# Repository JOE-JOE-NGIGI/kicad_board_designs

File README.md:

# kicad_board_designs
A repository of hardware design projects I have worked on.
Printed Circuit Boards(PCBs) have been designed using KiCad Version 5.1.12.

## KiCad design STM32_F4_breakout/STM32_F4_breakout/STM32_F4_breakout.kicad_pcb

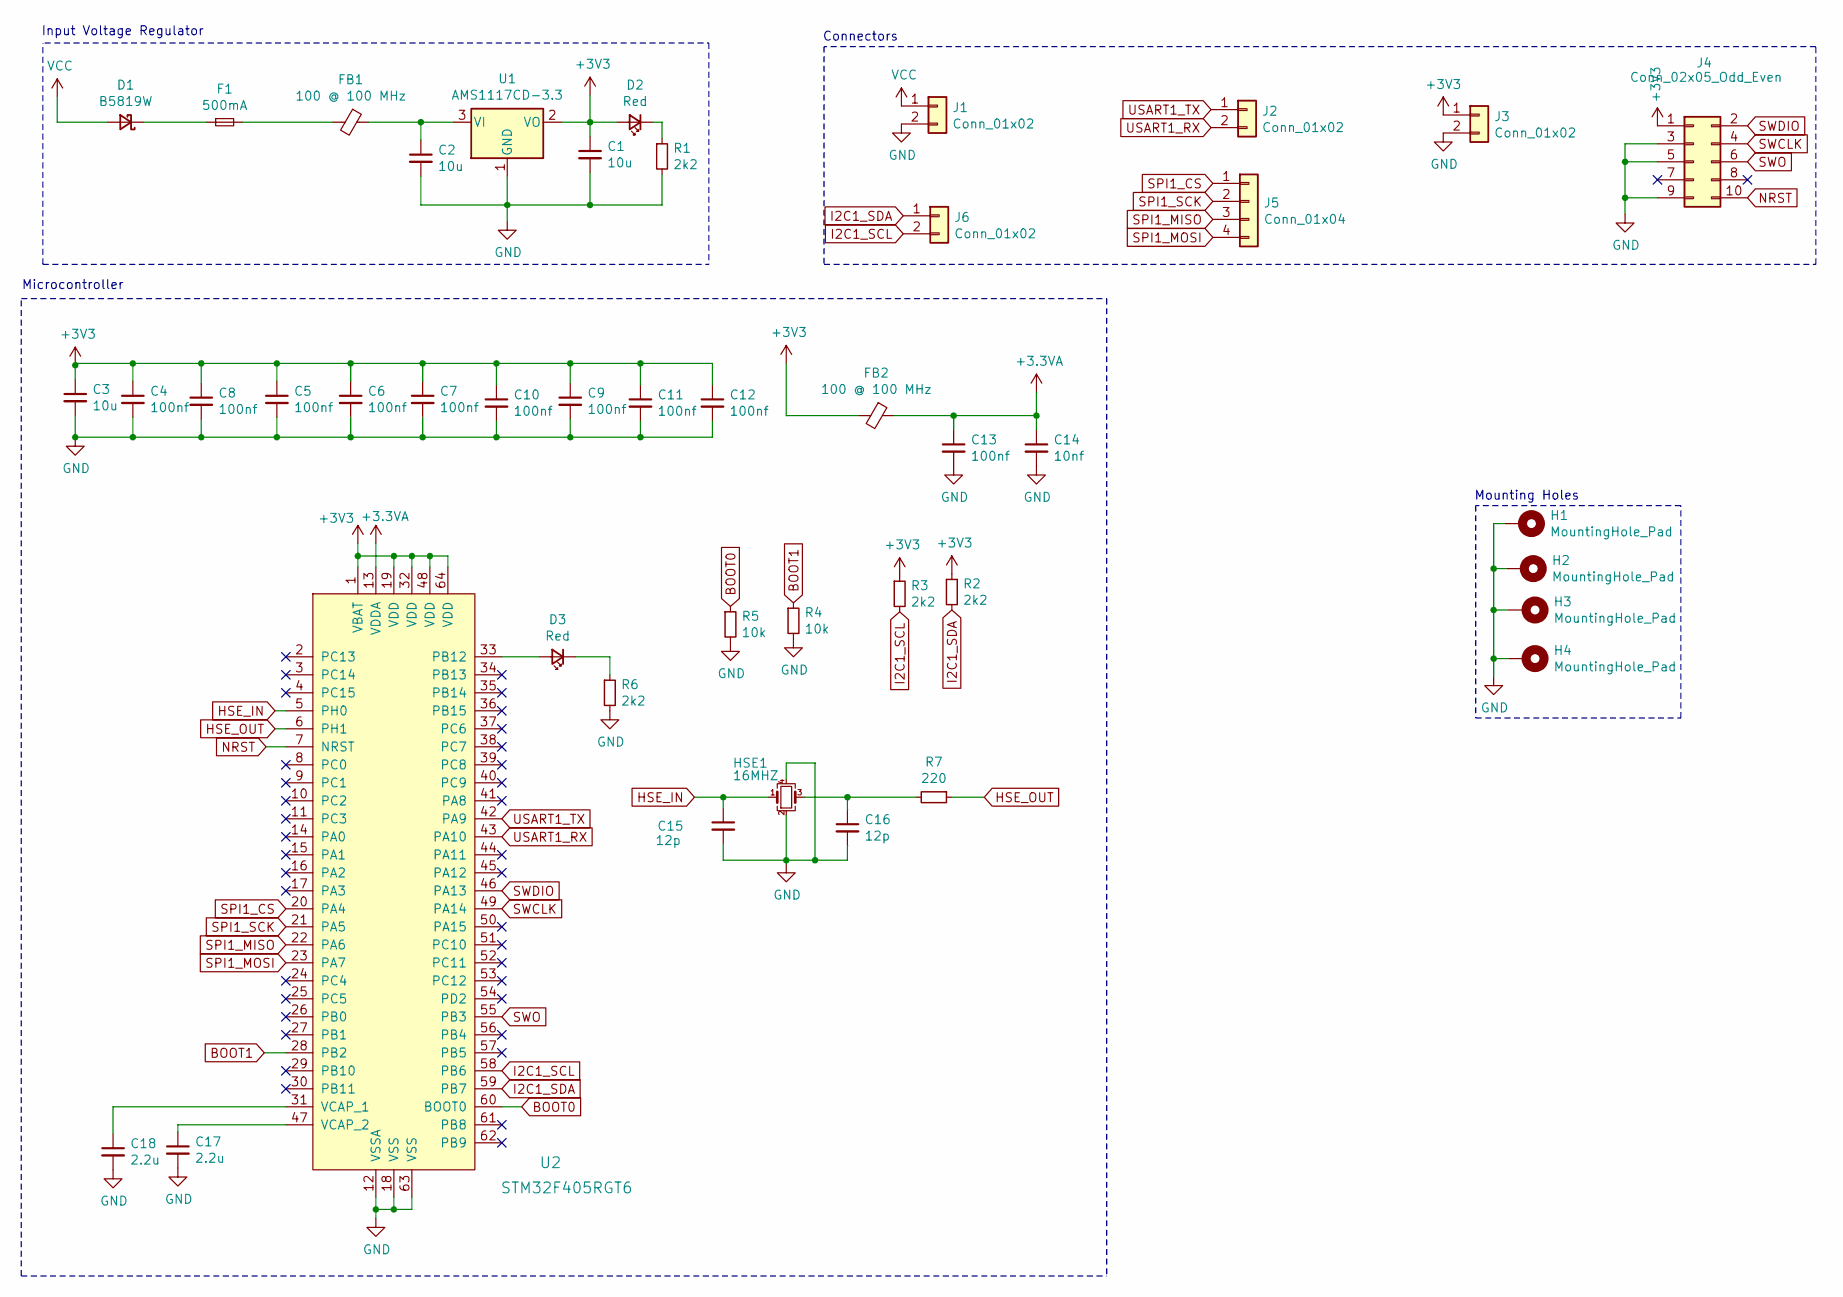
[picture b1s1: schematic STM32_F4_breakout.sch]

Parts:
C1, C2: 10u; C_0805_2012Metric
C3: 10u; C_0603_1608Metric
C4, C5, C6, C7, C8, C9, C10, C11, C12, C13: 100nf; C_0402_1005Metric
C14: 10nf; C_0402_1005Metric
C15, C16: 12p; C_0402_1005Metric
C17, C18: 2.2u; C_0603_1608Metric
D1: B5819W; D_SOD-123
D2, D3: Red; LED_0603_1608Metric
F1: 500mA; Fuse_0603_1608Metric
FB1, FB2: 100 @ 100 MHz; Fuse_0805_2012Metric
H1, H2, H3, H4: MountingHole_Pad; MountingHole_4.3mm_M4_Pad_Via
HSE1: 16MHZ; Crystal_SMD_3225-4Pin_3.2x2.5mm
J1, J2, J3, J6: Conn_01x02; PinHeader_1x02_P2.54mm_Vertical
J4: Conn_02x05_Odd_Even; PinHeader_2x05_P1.27mm_Vertical_SMD
J5: Conn_01x04; PinHeader_1x04_P2.54mm_Vertical
R1, R6: 2k2; R_0603_1608Metric
R2, R3: 2k2; R_0402_1005Metric
R4, R5: 10k; R_0402_1005Metric
R7: 220; R_0402_1005Metric
U1: AMS1117CD-3.3; TO-252-3_TabPin2
U2: STM32F405RGT6; LQFP-64_10x10mm; MPN STM32F405RGT6; Digi-Key_PN 497-11767-ND

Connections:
+3.3VA: C13.1, C14.1, FB2.1, U2.13 (VDDA)
+3V3: C1.1, C3.1, C4.1, C5.1, C6.1, C7.1, C8.1, C9.1, C10.1, C11.1, C12.1, D2.2 (A), FB2.2, J3.1, J4.1, R2.1, R3.1, U1.2 (VO), U2.1 (VBAT), U2.19 (VDD), U2.32 (VDD), U2.48 (VDD), U2.64 (VDD)
BOOT0: R5.1, U2.60 (BOOT0)
BOOT1: R4.1, U2.28 (PB2)
GND: C1.2, C2.2, C3.2, C4.2, C5.2, C6.2, C7.2, C8.2, C9.2, C10.2, C11.2, C12.2, C13.2, C14.2, C15.2, C16.2, C17.2, C18.2, H1.1, H2.1, H3.1, H4.1, HSE1.2, HSE1.4, J1.2, J3.2, J4.3, J4.5, J4.9, R1.2, R4.2, R5.2, R6.2, U1.1 (GND), U2.12 (VSSA), U2.18 (VSS), U2.63 (VSS)
HSE_IN: C15.1, HSE1.1, U2.5 (PH0)
HSE_OUT: R7.1, U2.6 (PH1)
I2C1_SCL: J6.2, R3.2, U2.58 (PB6)
I2C1_SDA: J6.1, R2.2, U2.59 (PB7)
NRST: J4.10, U2.7 (NRST)
unnamed: C2.1, FB1.1, U1.3 (VI)
unnamed: C16.1, HSE1.3, R7.2
unnamed: C17.1, U2.47 (VCAP_2)
unnamed: C18.1, U2.31 (VCAP_1)
unnamed: D1.1 (K), F1.1
unnamed: D2.1 (K), R1.1
unnamed: D3.1 (K), R6.1
unnamed: D3.2 (A), U2.33 (PB12)
unnamed: F1.2, FB1.2
SPI1_CS: J5.1, U2.20 (PA4)
SPI1_MISO: J5.3, U2.22 (PA6)
SPI1_MOSI: J5.4, U2.23 (PA7)
SPI1_SCK: J5.2, U2.21 (PA5)
SWCLK: J4.4, U2.49 (PA14)
SWDIO: J4.2, U2.46 (PA13)
SWO: J4.6, U2.55 (PB3)
USART1_RX: J2.2, U2.43 (PA10)
USART1_TX: J2.1, U2.42 (PA9)
VCC: D1.2 (A), J1.1

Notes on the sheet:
Input Voltage Regulator
Microcontroller
Connectors
Mounting Holes

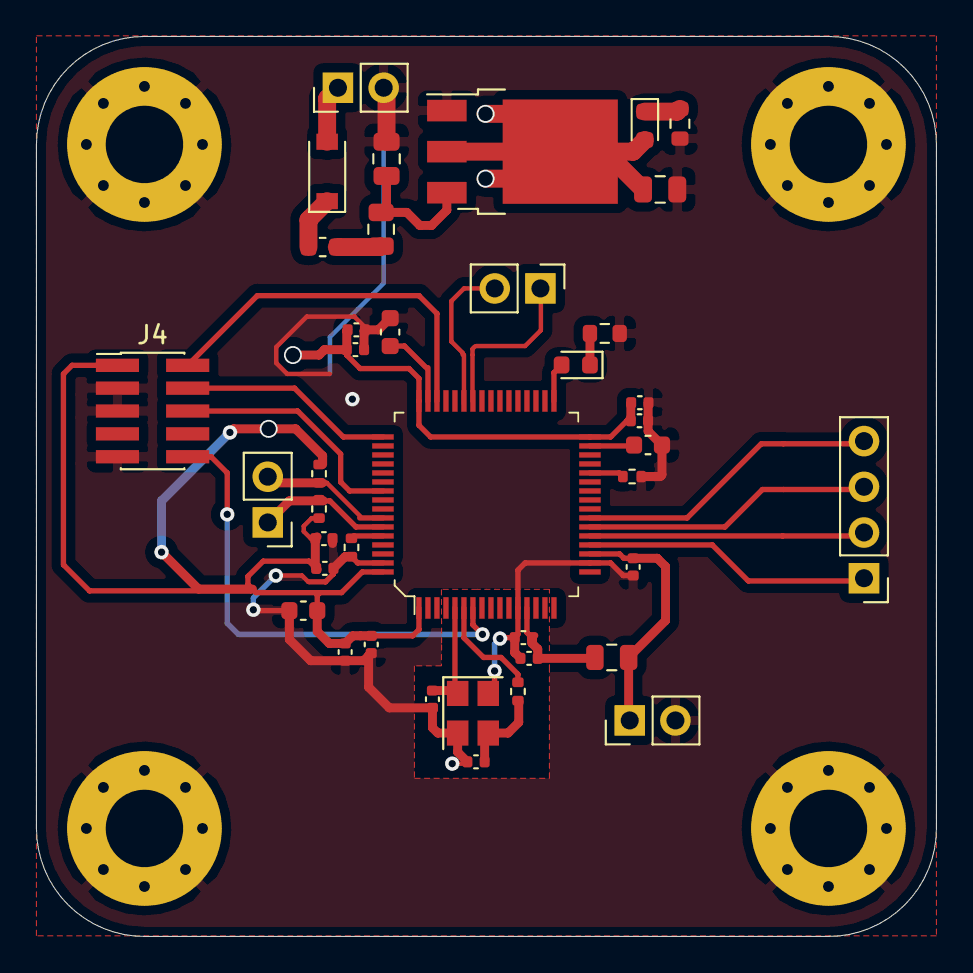
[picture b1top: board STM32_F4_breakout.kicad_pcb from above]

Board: 4 copper layers, 50.0 x 50.0 mm, 44 parts (0 on the bottom side), 29 nets.

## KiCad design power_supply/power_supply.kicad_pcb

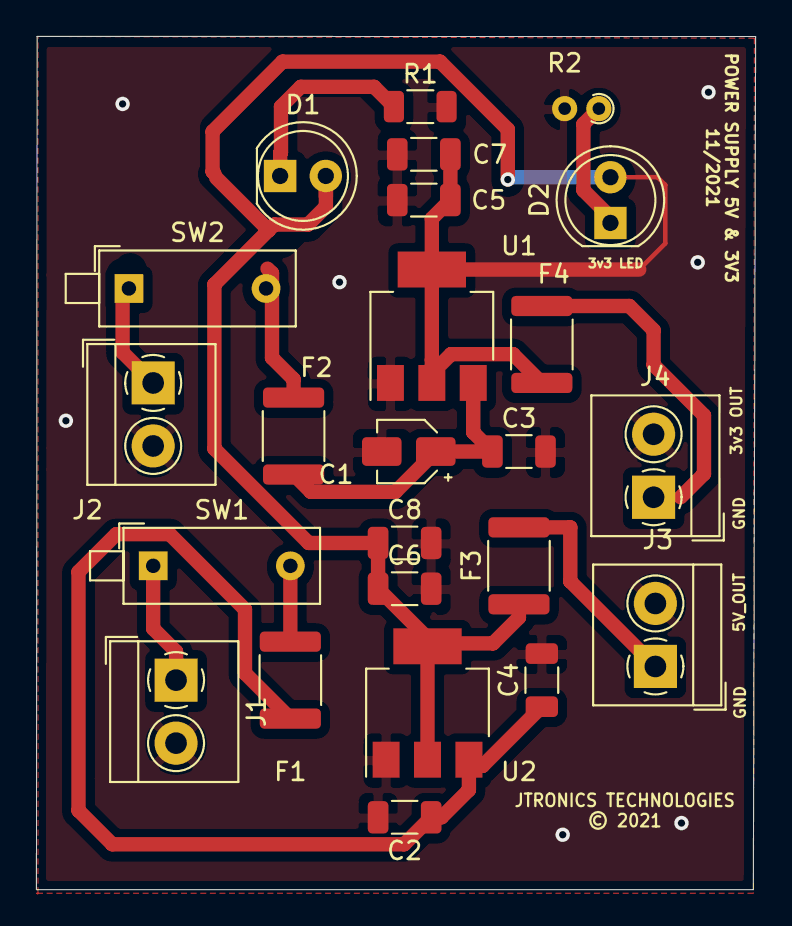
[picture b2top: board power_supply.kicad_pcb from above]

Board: 2 copper layers, 40.0 x 47.4 mm, 24 parts (0 on the bottom side), 12 nets.

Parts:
C1: 10u; CP_Elec_3x5.4
C2, C5, C6: 10u; C_1206_3216Metric
C3, C4: 100n; C_1206_3216Metric
C7, C8: 0.1u; C_1206_3216Metric
D1, D2: LED_Small; LED_D5.0mm
F1, F2, F3, F4: Fuse_Small; Fuse_1812_4532Metric
J1, J2, J3, J4: Conn_01x02; TerminalBlock_4Ucon_1x02_P3.50mm_Horizontal
R1: 1k; R_1206_3216Metric
R2: 1k; R_Axial_DIN0204_L3.6mm_D1.6mm_P1.90mm_Vertical
SW1, SW2: SW_DIP_x01; SW_DIP_SPSTx01_Piano_10.8x4.1mm_W7.62mm_P2.54mm
U1: LD1117S33TR_SOT223; SOT-223-3_TabPin2
U2: LD1117S50TR_SOT223; SOT-223-3_TabPin2

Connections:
+3V3: C5.1, C6.1, C7.1, C8.1, D1.2, D2.2, F3.1, F4.1, U1.2, U2.2
/3v3_out: F4.2, J4.1
/5V_out: F3.2, J3.1
GND: C1.2, C2.2, C3.2, C4.2, C5.2, C6.2, C7.2, C8.2, J1.2, J2.2, J3.2, J4.2, R1.2, R2.2, U1.1, U2.1
unnamed: C1.1, C3.1, F2.2, U1.3
unnamed: C2.1, C4.1, F1.2, U2.3
unnamed: D1.1, R1.1
unnamed: D2.1, R2.1
unnamed: F1.1, SW1.2
unnamed: F2.1, SW2.2
unnamed: J1.1, SW1.1
unnamed: J2.1, SW2.1

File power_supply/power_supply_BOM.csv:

"Id";"Designator";"Package";"Quantity";"Designation";"Supplier and ref";
1;"J2,J1,J3,J4";"TerminalBlock_4Ucon_1x02_P3.50mm_Horizontal";4;"Conn_01x02";;;
2;"C1";"CP_Elec_3x5.4";1;"10u";;;
3;"C2,C5,C6";"C_1206_3216Metric";3;"10u";;;
4;"C3,C4";"C_1206_3216Metric";2;"100n";;;
5;"C7,C8";"C_1206_3216Metric";2;"0.1u";;;
6;"D1,D2";"LED_D5.0mm";2;"LED_Small";;;
7;"F1,F2,F3,F4";"Fuse_1812_4532Metric";4;"Fuse_Small";;;
8;"R1";"R_1206_3216Metric";1;"1k";;;
9;"R2";"R_Axial_DIN0204_L3.6mm_D1.6mm_P1.90mm_Vertical";1;"1k";;;
10;"SW1,SW2";"SW_DIP_SPSTx01_Piano_10.8x4.1mm_W7.62mm_P2.54mm";2;"SW_DIP_x01";;;
11;"U1";"SOT-223-3_TabPin2";1;"LD1117S33TR_SOT223";;;
12;"U2";"SOT-223-3_TabPin2";1;"LD1117S50TR_SOT223";;;

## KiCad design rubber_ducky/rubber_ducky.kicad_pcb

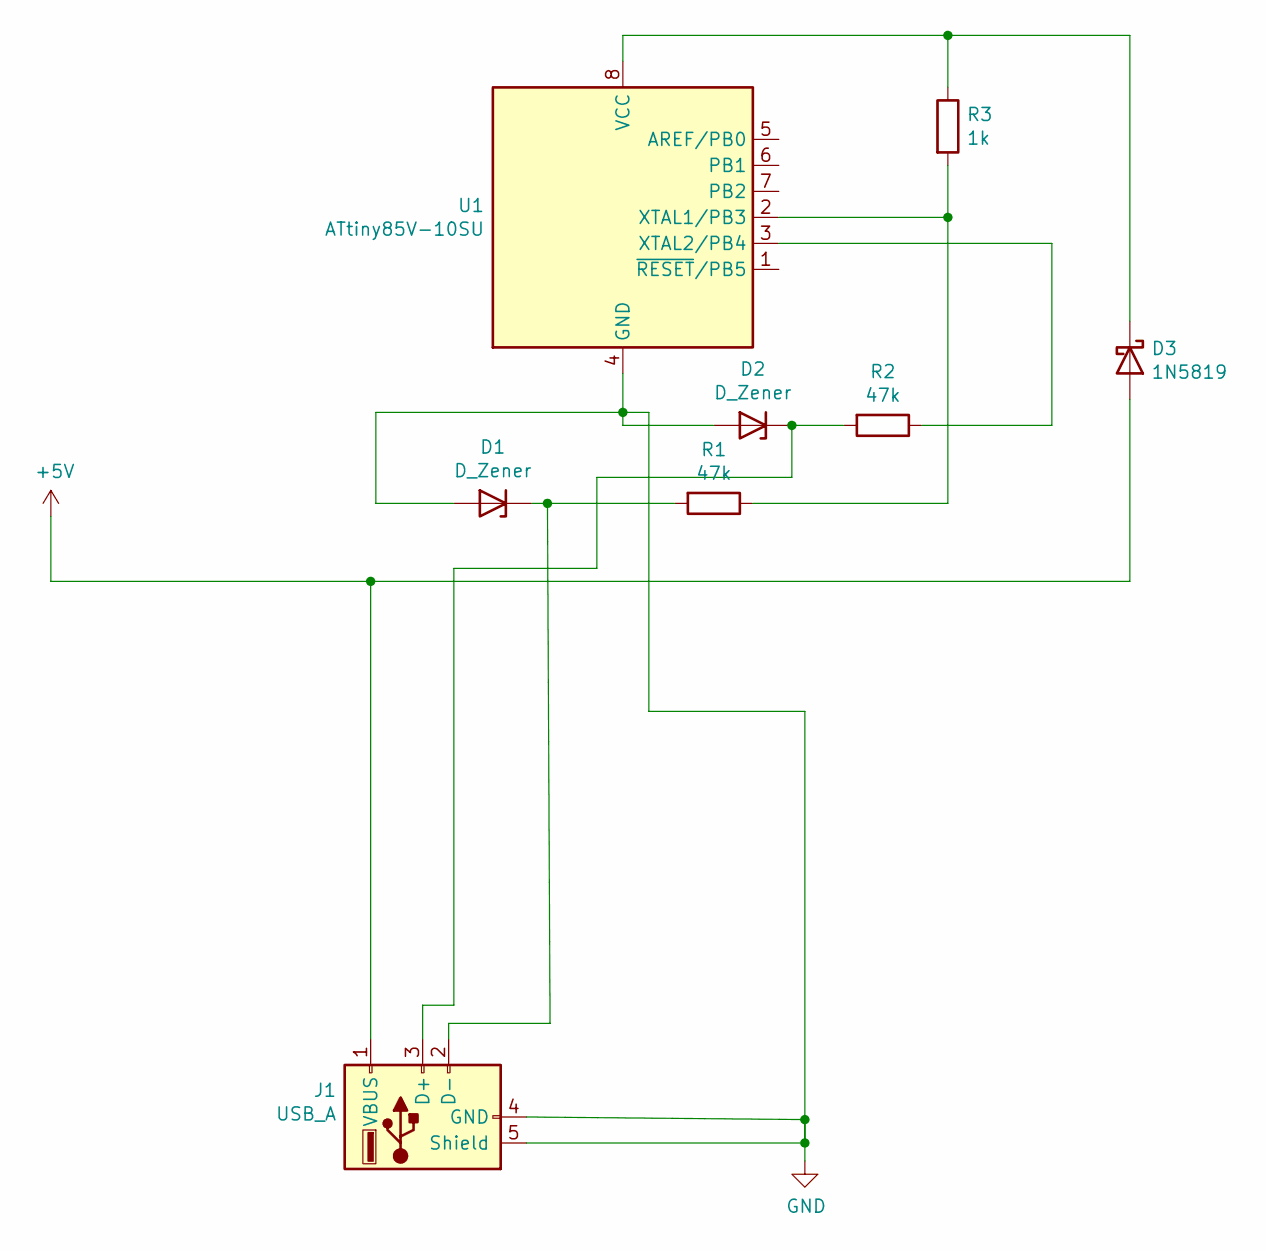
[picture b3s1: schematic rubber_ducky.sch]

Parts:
D1, D2: D_Zener; D_0805_2012Metric
D3: 1N5819; D_DO-41_SOD81_P10.16mm_Horizontal
J1: USB_A; USB3_A_Molex_48393-001
R1, R2: 47k; R_1206_3216Metric_Pad1.30x1.75mm_HandSolder
R3: 1k; R_1206_3216Metric_Pad1.30x1.75mm_HandSolder
U1: ATtiny85V-10SU; SOIJ-8_5.3x5.3mm_P1.27mm

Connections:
+5V: D3.2 (A), J1.1 (VBUS)
GND: D1.2 (A), D2.2 (A), J1.4 (GND), J1.5 (Shield), U1.4 (GND)
unnamed: D1.1 (K), J1.2 (D-), R1.2
unnamed: D2.1 (K), J1.3 (D+), R2.2
unnamed: D3.1 (K), R3.1, U1.8 (VCC)
unnamed: R1.1, R3.2, U1.2 (XTAL1/PB3)
unnamed: R2.1, U1.3 (XTAL2/PB4)

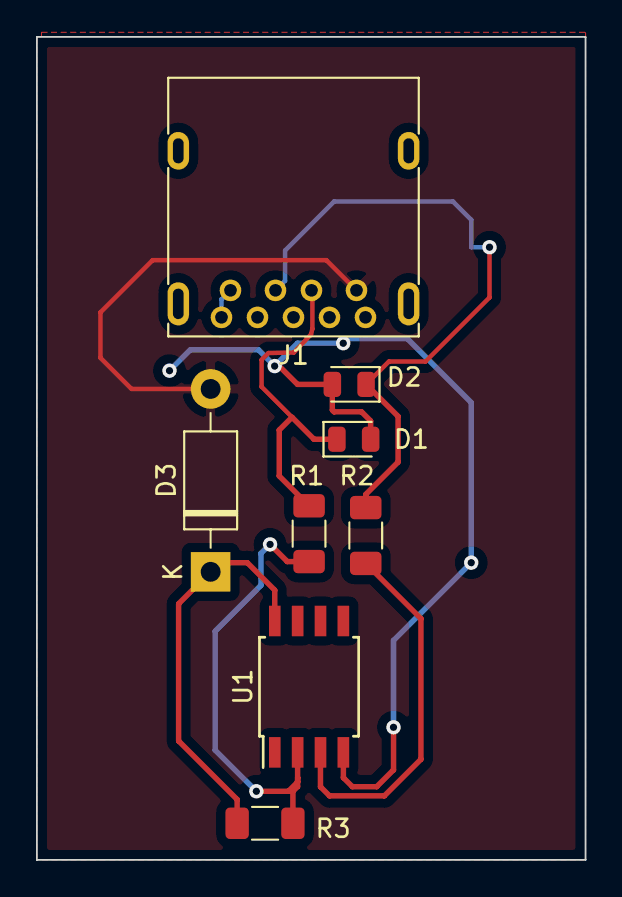
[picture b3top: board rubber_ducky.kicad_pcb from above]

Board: 2 copper layers, 30.5 x 45.7 mm, 8 parts (0 on the bottom side), 7 nets.

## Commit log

2021-12-06 add project files
2021-12-06 add images
2021-12-06 add chip footprint
2021-12-06 add README.md

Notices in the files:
power_supply/power_supply.kicad_pcb:
© 2021
